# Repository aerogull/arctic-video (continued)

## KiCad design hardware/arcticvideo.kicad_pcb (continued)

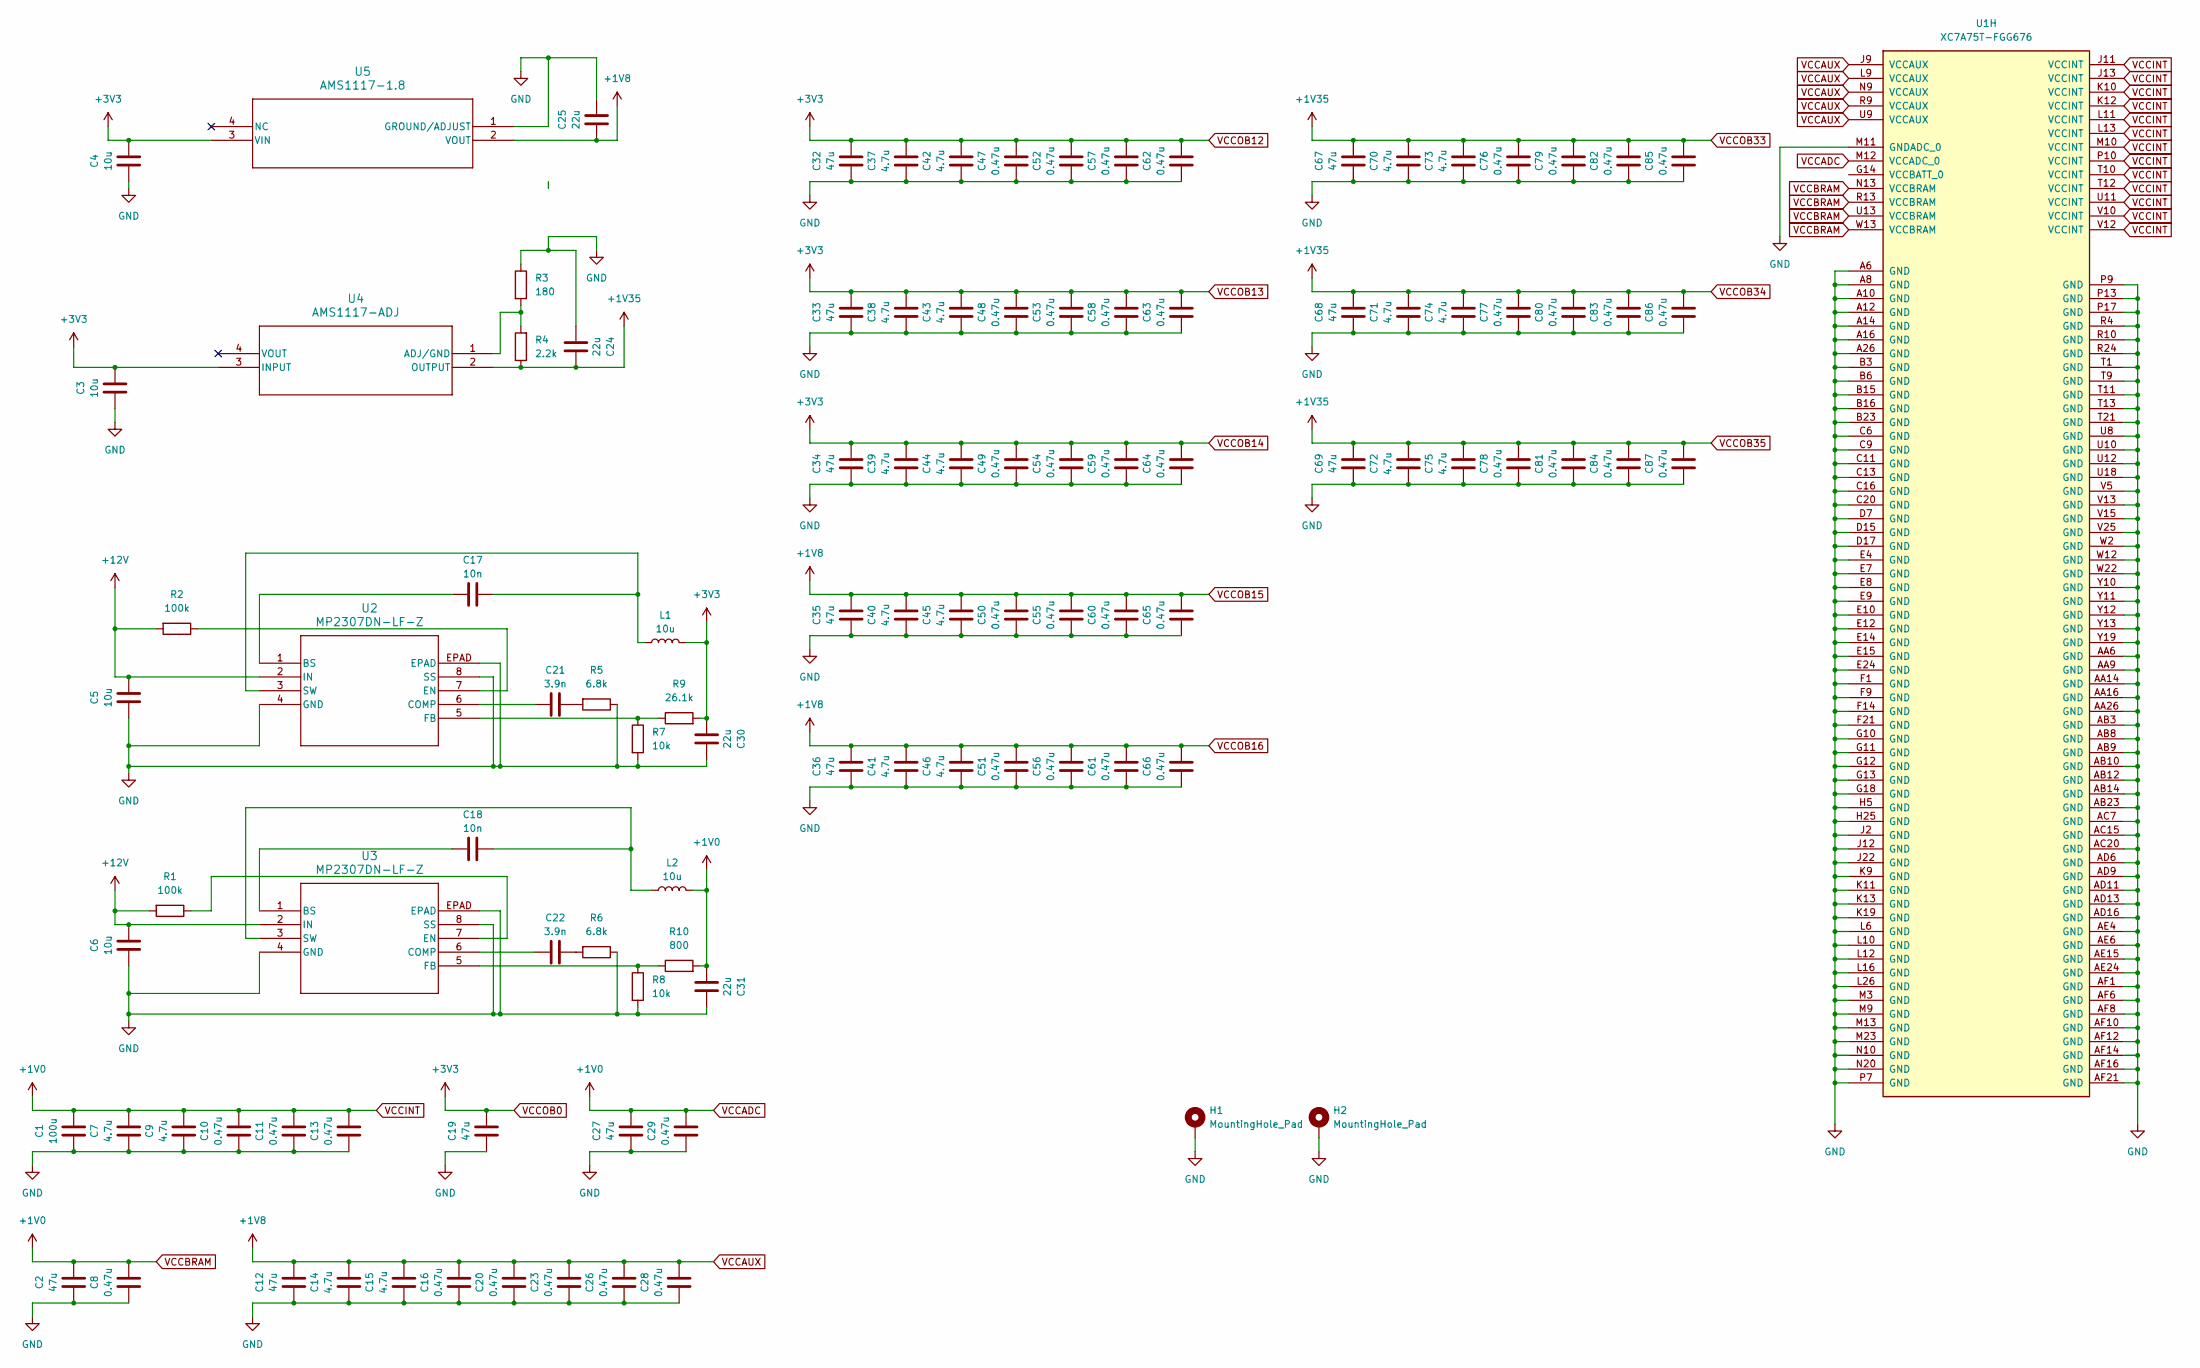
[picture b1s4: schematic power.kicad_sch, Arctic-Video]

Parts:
C1: 100u; C_0402_1005Metric
C2: 47u; C_0402_1005Metric
C3, C4, C5, C6: 10u; C_0402_1005Metric
C7, C9, C14, C15, C37, C38, C39, C40, C41, C42, C43, C44, C45, C46, C70, C71, C72, C73, C74, C75: 4.7u; C_0402_1005Metric
C8, C10, C11, C13, C16, C20, C23, C26, C28, C29, C47, C48, C49, C50, C51, C52, C53, C54, C55, C56, C57, C58, C59, C60, C61, C62, C63, C64, C65, C66, C76, C77, C78, C79, C80, C81, C82, C83, C84, C85, C86, C87: 0.47u; C_0402_1005Metric
C12, C19, C27, C32, C33, C34, C35, C36, C67, C68, C69: 47u; C_0603_1608Metric
C17, C18: 10n; C_0402_1005Metric
C21, C22: 3.9n; C_0402_1005Metric
C24, C25, C30, C31: 22u; C_0402_1005Metric
H1: MountingHole_Pad; MountingHole_2.7mm_Pad_Via
H2: MountingHole_Pad; MountingHole_3mm_Pad_Via
L1, L2: 10u; L_0402_1005Metric
R1, R2: 100k; R_0402_1005Metric
R3: 180; R_0402_1005Metric
R4: 2.2k; R_0402_1005Metric
R5, R6: 6.8k; R_0402_1005Metric
R7, R8: 10k; R_0402_1005Metric
R9: 26.1k; R_0402_1005Metric
R10: 800; R_0402_1005Metric
U1: XC7A75T-FGG676; Xilinx_FGG676
U2, U3: MP2307DN-LF-Z; IC8_MP2307_MNP
U4: AMS1117-ADJ; SOT_AMS1117-2.5_AMS
U5: AMS1117-1.8; SOT223_AMS1117-1.8_AMS

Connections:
+12V: C5.2, C6.2, R1.2, R2.2, U2.2 (IN), U3.2 (IN); also elsewhere on the board
GND: C1.1, C2.1, C3.1, C4.1, C5.1, C6.1, C7.1, C8.1, C9.1, C10.1, C11.1, C12.1, C13.1, C14.1, C15.1, C16.1, C19.1, C20.1, C23.1, C24.1, C25.2, C26.1, C27.1, C28.1, C29.1, C30.2, C31.2, C32.1, C33.1, C34.1, C35.1, C36.1, C37.1, C38.1, C39.1, C40.1, C41.1, C42.1, C43.1, C44.1, C45.1, C46.1, C47.1, C48.1, C49.1, C50.1, C51.1, C52.1, C53.1, C54.1, C55.1, C56.1, C57.1, C58.1, C59.1, C60.1, C61.1, C62.1, C63.1, C64.1, C65.1, C66.1, C67.1, C68.1, C69.1, C70.1, C71.1, C72.1, C73.1, C74.1, C75.1, C76.1, C77.1, C78.1, C79.1, C80.1, C81.1, C82.1, C83.1, C84.1, C85.1, C86.1, C87.1, H1.1 (1_1), H2.1 (1_1), R3.1, R5.1, R6.1, R7.2, R8.2, U1.A6 (GND), U1.A8 (GND), U1.A10 (GND), U1.A12 (GND), U1.A14 (GND), U1.A16 (GND), U1.A26 (GND), U1.AA6 (GND), U1.AA9 (GND), U1.AA14 (GND), U1.AA16 (GND), U1.AA26 (GND), U1.AB3 (GND), U1.AB8 (GND), U1.AB9 (GND), U1.AB10 (GND), U1.AB12 (GND), U1.AB14 (GND), U1.AB23 (GND), U1.AC7 (GND), U1.AC15 (GND), U1.AC20 (GND), U1.AD6 (GND), U1.AD9 (GND), U1.AD11 (GND), U1.AD13 (GND), U1.AD16 (GND), U1.AE4 (GND), U1.AE6 (GND), U1.AE15 (GND), U1.AE24 (GND), U1.AF1 (GND), U1.AF6 (GND), U1.AF8 (GND), U1.AF10 (GND), U1.AF12 (GND), U1.AF14 (GND), U1.AF16 (GND), U1.AF21 (GND), U1.B3 (GND), U1.B6 (GND), U1.B15 (GND), U1.B16 (GND), U1.B23 (GND), U1.C6 (GND), U1.C9 (GND), U1.C11 (GND), U1.C13 (GND), U1.C16 (GND), U1.C20 (GND), U1.D7 (GND), U1.D15 (GND), U1.D17 (GND), U1.E4 (GND), U1.E7 (GND), U1.E8 (GND), U1.E9 (GND), U1.E10 (GND), U1.E12 (GND), U1.E14 (GND), U1.E15 (GND), U1.E24 (GND), U1.F1 (GND), U1.F9 (GND), U1.F14 (GND), U1.F21 (GND), U1.G10 (GND), U1.G11 (GND), U1.G12 (GND), U1.G13 (GND), U1.G18 (GND), U1.H5 (GND), U1.H25 (GND), U1.J2 (GND), U1.J12 (GND), U1.J22 (GND), U1.K9 (GND), U1.K11 (GND), U1.K13 (GND), U1.K19 (GND), U1.L6 (GND), U1.L10 (GND), U1.L12 (GND), U1.L16 (GND), U1.L26 (GND), U1.M3 (GND), U1.M9 (GND), U1.M11 (GNDADC_0), U1.M13 (GND), U1.M23 (GND), U1.N10 (GND), U1.N20 (GND), U1.P7 (GND), U1.P9 (GND), U1.P13 (GND), U1.P17 (GND), U1.R4 (GND), U1.R10 (GND), U1.R24 (GND), U1.T1 (GND), U1.T9 (GND), U1.T11 (GND), U1.T13 (GND), U1.T21 (GND), U1.U8 (GND), U1.U10 (GND), U1.U12 (GND), U1.U18 (GND), U1.V5 (GND), U1.V13 (GND), U1.V15 (GND), U1.V25 (GND), U1.W2 (GND), U1.W12 (GND), U1.W22 (GND), U1.Y10 (GND), U1.Y11 (GND), U1.Y12 (GND), U1.Y13 (GND), U1.Y19 (GND), U2.4 (GND), U2.8 (SS), U2.EPAD, U3.4 (GND), U3.8 (SS), U3.EPAD, U5.1 (GROUND/ADJUST); also elsewhere on the board
unnamed: C21.2, R5.2
unnamed: C22.2, R6.2
unnamed: C17.1, U2.1 (BS)
unnamed: C21.1, U2.6 (COMP)
unnamed: R2.1, U2.7 (EN)
unnamed: R7.1, R9.1, U2.5 (FB)
unnamed: C17.2, L1.1, U2.3 (SW)
unnamed: C18.1, U3.1 (BS)
unnamed: C22.1, U3.6 (COMP)
unnamed: R1.1, U3.7 (EN)
unnamed: R8.1, R10.1, U3.5 (FB)
unnamed: C18.2, L2.1, U3.3 (SW)
unnamed: R3.2, R4.2, U4.1 (ADJ/GND)
VCCADC: C1.2, C2.2, C7.2, C8.2, C9.2, C10.2, C11.2, C13.2, C27.2, C29.2, C31.1, L2.2, R10.2, U1.J11 (VCCINT), U1.J13 (VCCINT), U1.K10 (VCCINT), U1.K12 (VCCINT), U1.L11 (VCCINT), U1.L13 (VCCINT), U1.M10 (VCCINT), U1.M12 (VCCADC_0), U1.N13 (VCCBRAM), U1.P10 (VCCINT), U1.R13 (VCCBRAM), U1.T10 (VCCINT), U1.T12 (VCCINT), U1.U11 (VCCINT), U1.U13 (VCCBRAM), U1.V10 (VCCINT), U1.V12 (VCCINT), U1.W13 (VCCBRAM)
VCCAUX: C12.2, C14.2, C15.2, C16.2, C20.2, C23.2, C25.1, C26.2, C28.2, C35.2, C36.2, C40.2, C41.2, C45.2, C46.2, C50.2, C51.2, C55.2, C56.2, C60.2, C61.2, C65.2, C66.2, U1.J9 (VCCAUX), U1.L9 (VCCAUX), U1.N9 (VCCAUX), U1.R9 (VCCAUX), U1.U9 (VCCAUX), U5.2 (VOUT); also elsewhere on the board
VCCOB0: C3.2, C4.2, C19.2, C30.1, C32.2, C33.2, C34.2, C37.2, C38.2, C39.2, C42.2, C43.2, C44.2, C47.2, C48.2, C49.2, C52.2, C53.2, C54.2, C57.2, C58.2, C59.2, C62.2, C63.2, C64.2, L1.2, R9.2, U4.3 (INPUT), U5.3 (VIN); also elsewhere on the board
VCCOB33: C24.2, C67.2, C68.2, C69.2, C70.2, C71.2, C72.2, C73.2, C74.2, C75.2, C76.2, C77.2, C78.2, C79.2, C80.2, C81.2, C82.2, C83.2, C84.2, C85.2, C86.2, C87.2, R4.1, U4.2 (OUTPUT); also elsewhere on the board

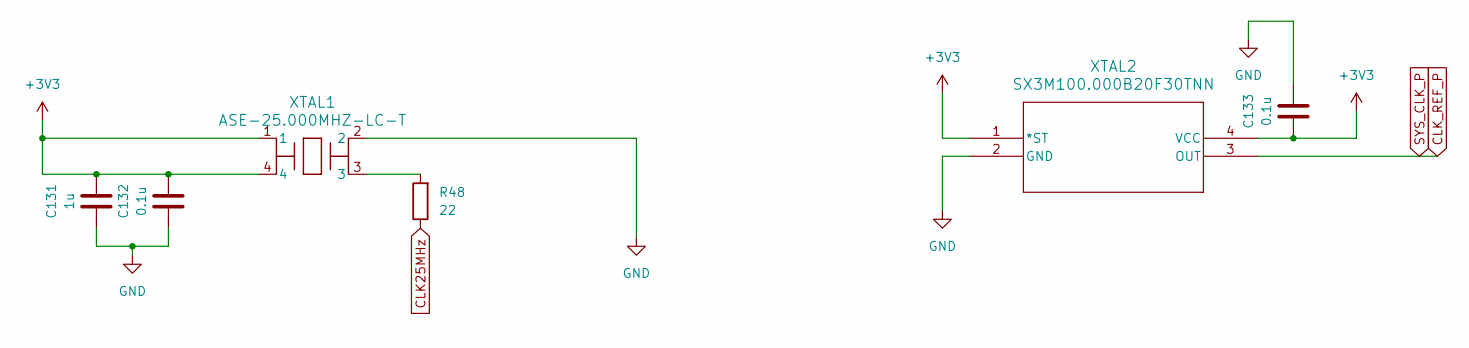
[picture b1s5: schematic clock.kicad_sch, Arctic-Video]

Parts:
C131: 1u; C_0402_1005Metric
C132, C133: 0.1u; C_0402_1005Metric
R48: 22; R_0402_1005Metric
XTAL1: ASE-25.000MHZ-LC-T; CHIP_ASE-24_ABR
XTAL2: SX3M100.000B20F30TNN; SG-210STF_EPS

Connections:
CLK25MHz: R48.1; also elsewhere on the board
CLK_REF_P: XTAL2.3 (OUT); also elsewhere on the board
GND: C131.1, C132.1, C133.2, XTAL1.2, XTAL2.2 (GND); also elsewhere on the board
unnamed: R48.2, XTAL1.3
VCCOB0: C131.2, C132.2, C133.1, XTAL1.1, XTAL1.4, XTAL2.1 (*ST), XTAL2.4 (VCC); also elsewhere on the board

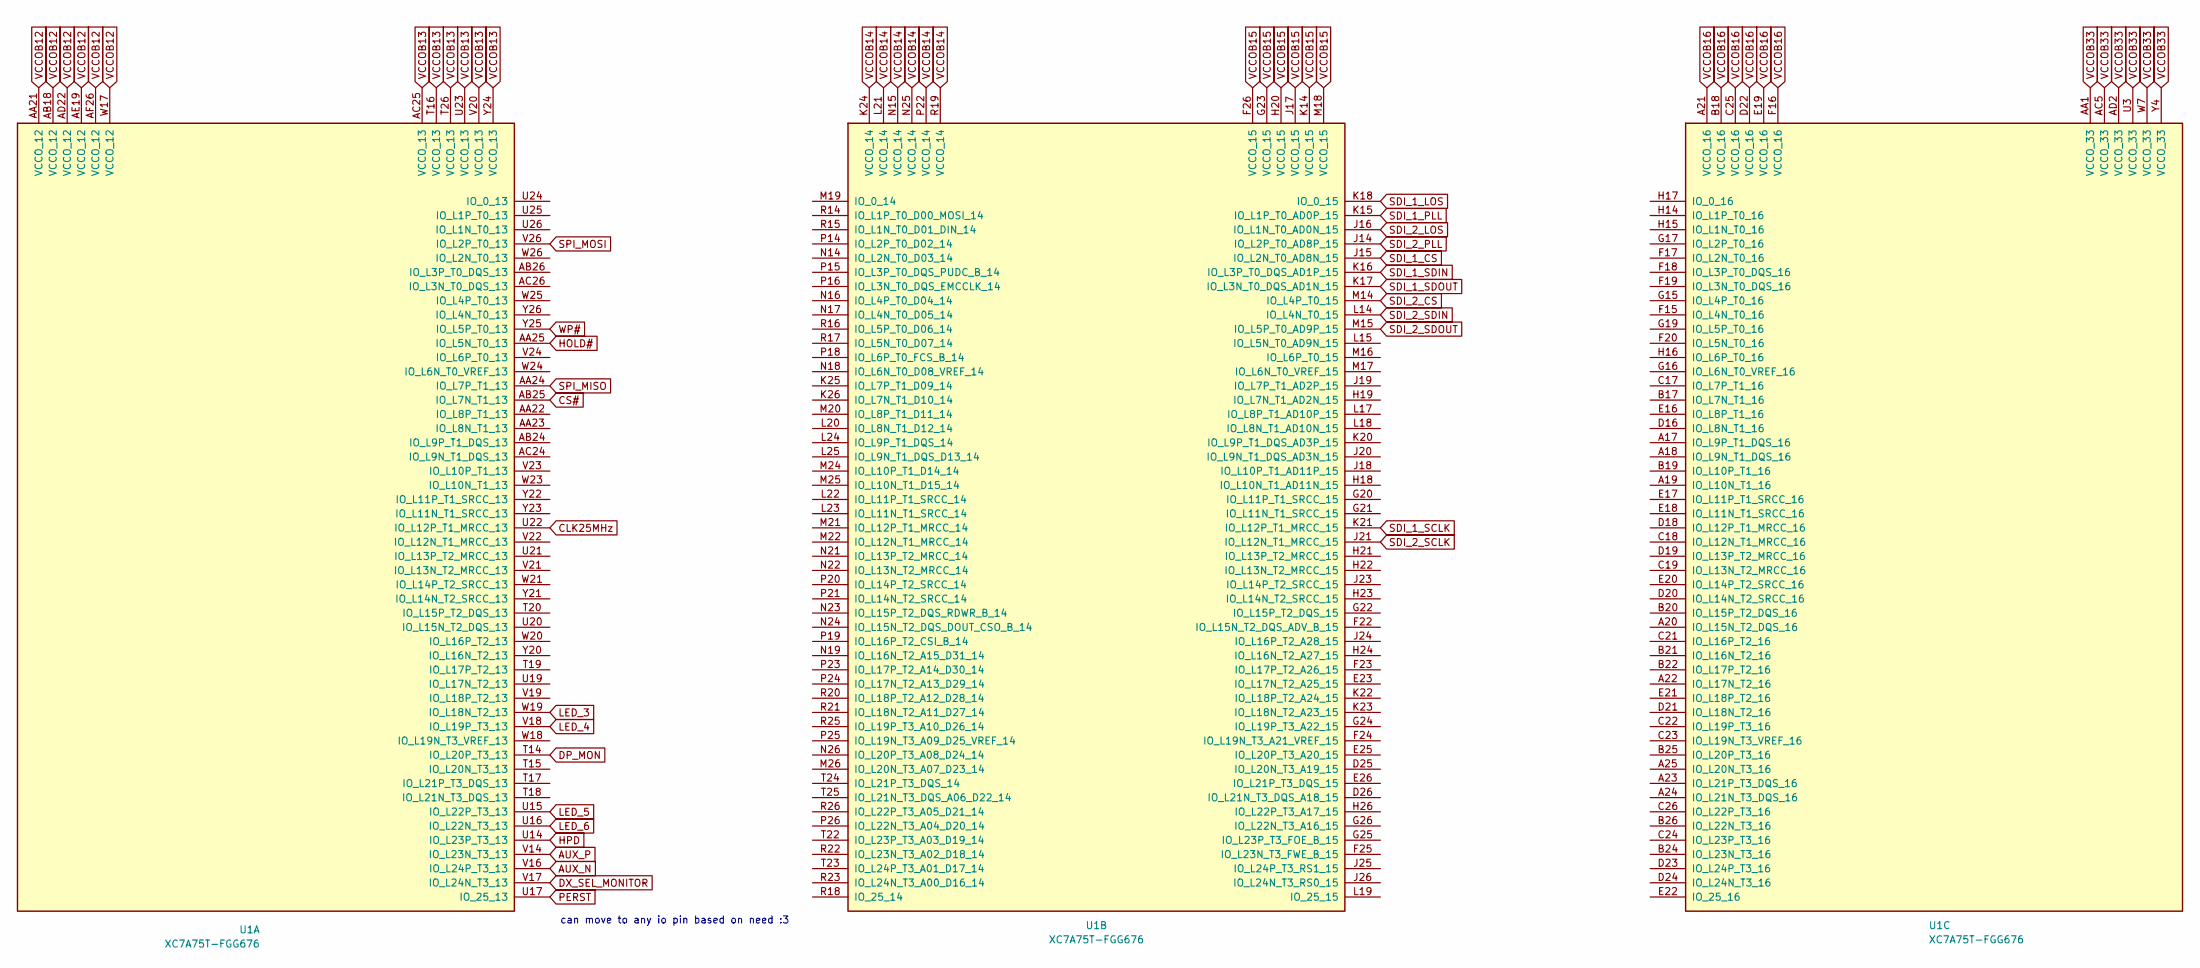
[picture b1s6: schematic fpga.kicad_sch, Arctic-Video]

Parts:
U1: XC7A75T-FGG676; Xilinx_FGG676

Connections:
AUX_N: U1.V16 (IO_L24P_T3_13); also elsewhere on the board
AUX_P: U1.V14 (IO_L23N_T3_13); also elsewhere on the board
CLK25MHz: U1.U22 (IO_L12P_T1_MRCC_13); also elsewhere on the board
CS#: U1.AB25 (IO_L7N_T1_13); also elsewhere on the board
DP_MON: U1.T14 (IO_L20P_T3_13); also elsewhere on the board
DX_SEL_MONITOR: U1.V17 (IO_L24N_T3_13); also elsewhere on the board
HOLD#: U1.AA25 (IO_L5N_T0_13); also elsewhere on the board
HPD: U1.U14 (IO_L23P_T3_13); also elsewhere on the board
LED_3: U1.W19 (IO_L18N_T2_13); also elsewhere on the board
LED_4: U1.V18 (IO_L19P_T3_13); also elsewhere on the board
LED_5: U1.U15 (IO_L22P_T3_13); also elsewhere on the board
LED_6: U1.U16 (IO_L22N_T3_13); also elsewhere on the board
PERST: U1.U17 (IO_25_13); also elsewhere on the board
SDI_1_CS: U1.J15 (IO_L2N_T0_AD8N_15); also elsewhere on the board
SDI_1_LOS: U1.K18 (IO_0_15); also elsewhere on the board
SDI_1_PLL: U1.K15 (IO_L1P_T0_AD0P_15); also elsewhere on the board
SDI_1_SCLK: U1.K21 (IO_L12P_T1_MRCC_15); also elsewhere on the board
SDI_1_SDIN: U1.K16 (IO_L3P_T0_DQS_AD1P_15); also elsewhere on the board
SDI_1_SDOUT: U1.K17 (IO_L3N_T0_DQS_AD1N_15); also elsewhere on the board
SDI_2_CS: U1.M14 (IO_L4P_T0_15); also elsewhere on the board
SDI_2_LOS: U1.J16 (IO_L1N_T0_AD0N_15); also elsewhere on the board
SDI_2_PLL: U1.J14 (IO_L2P_T0_AD8P_15); also elsewhere on the board
SDI_2_SCLK: U1.J21 (IO_L12N_T1_MRCC_15); also elsewhere on the board
SDI_2_SDIN: U1.L14 (IO_L4N_T0_15); also elsewhere on the board
SDI_2_SDOUT: U1.M15 (IO_L5P_T0_AD9P_15); also elsewhere on the board
SPI_MISO: U1.AA24 (IO_L7P_T1_13); also elsewhere on the board
SPI_MOSI: U1.V26 (IO_L2P_T0_13); also elsewhere on the board
VCCAUX: U1.A21 (VCCO_16), U1.B18 (VCCO_16), U1.C25 (VCCO_16), U1.D22 (VCCO_16), U1.E19 (VCCO_16), U1.F16 (VCCO_16), U1.F26 (VCCO_15), U1.G23 (VCCO_15), U1.H20 (VCCO_15), U1.J17 (VCCO_15), U1.K14 (VCCO_15), U1.M18 (VCCO_15); also elsewhere on the board
VCCOB0: U1.AA21 (VCCO_12), U1.AB18 (VCCO_12), U1.AC25 (VCCO_13), U1.AD22 (VCCO_12), U1.AE19 (VCCO_12), U1.AF26 (VCCO_12), U1.K24 (VCCO_14), U1.L21 (VCCO_14), U1.N15 (VCCO_14), U1.N25 (VCCO_14), U1.P22 (VCCO_14), U1.R19 (VCCO_14), U1.T16 (VCCO_13), U1.T26 (VCCO_13), U1.U23 (VCCO_13), U1.V20 (VCCO_13), U1.W17 (VCCO_12), U1.Y24 (VCCO_13); also elsewhere on the board
VCCOB33: U1.AA1 (VCCO_33), U1.AC5 (VCCO_33), U1.AD2 (VCCO_33), U1.U3 (VCCO_33), U1.W7 (VCCO_33), U1.Y4 (VCCO_33); also elsewhere on the board
WP#: U1.Y25 (IO_L5P_T0_13); also elsewhere on the board

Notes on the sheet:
can move to any io pin based on need :3

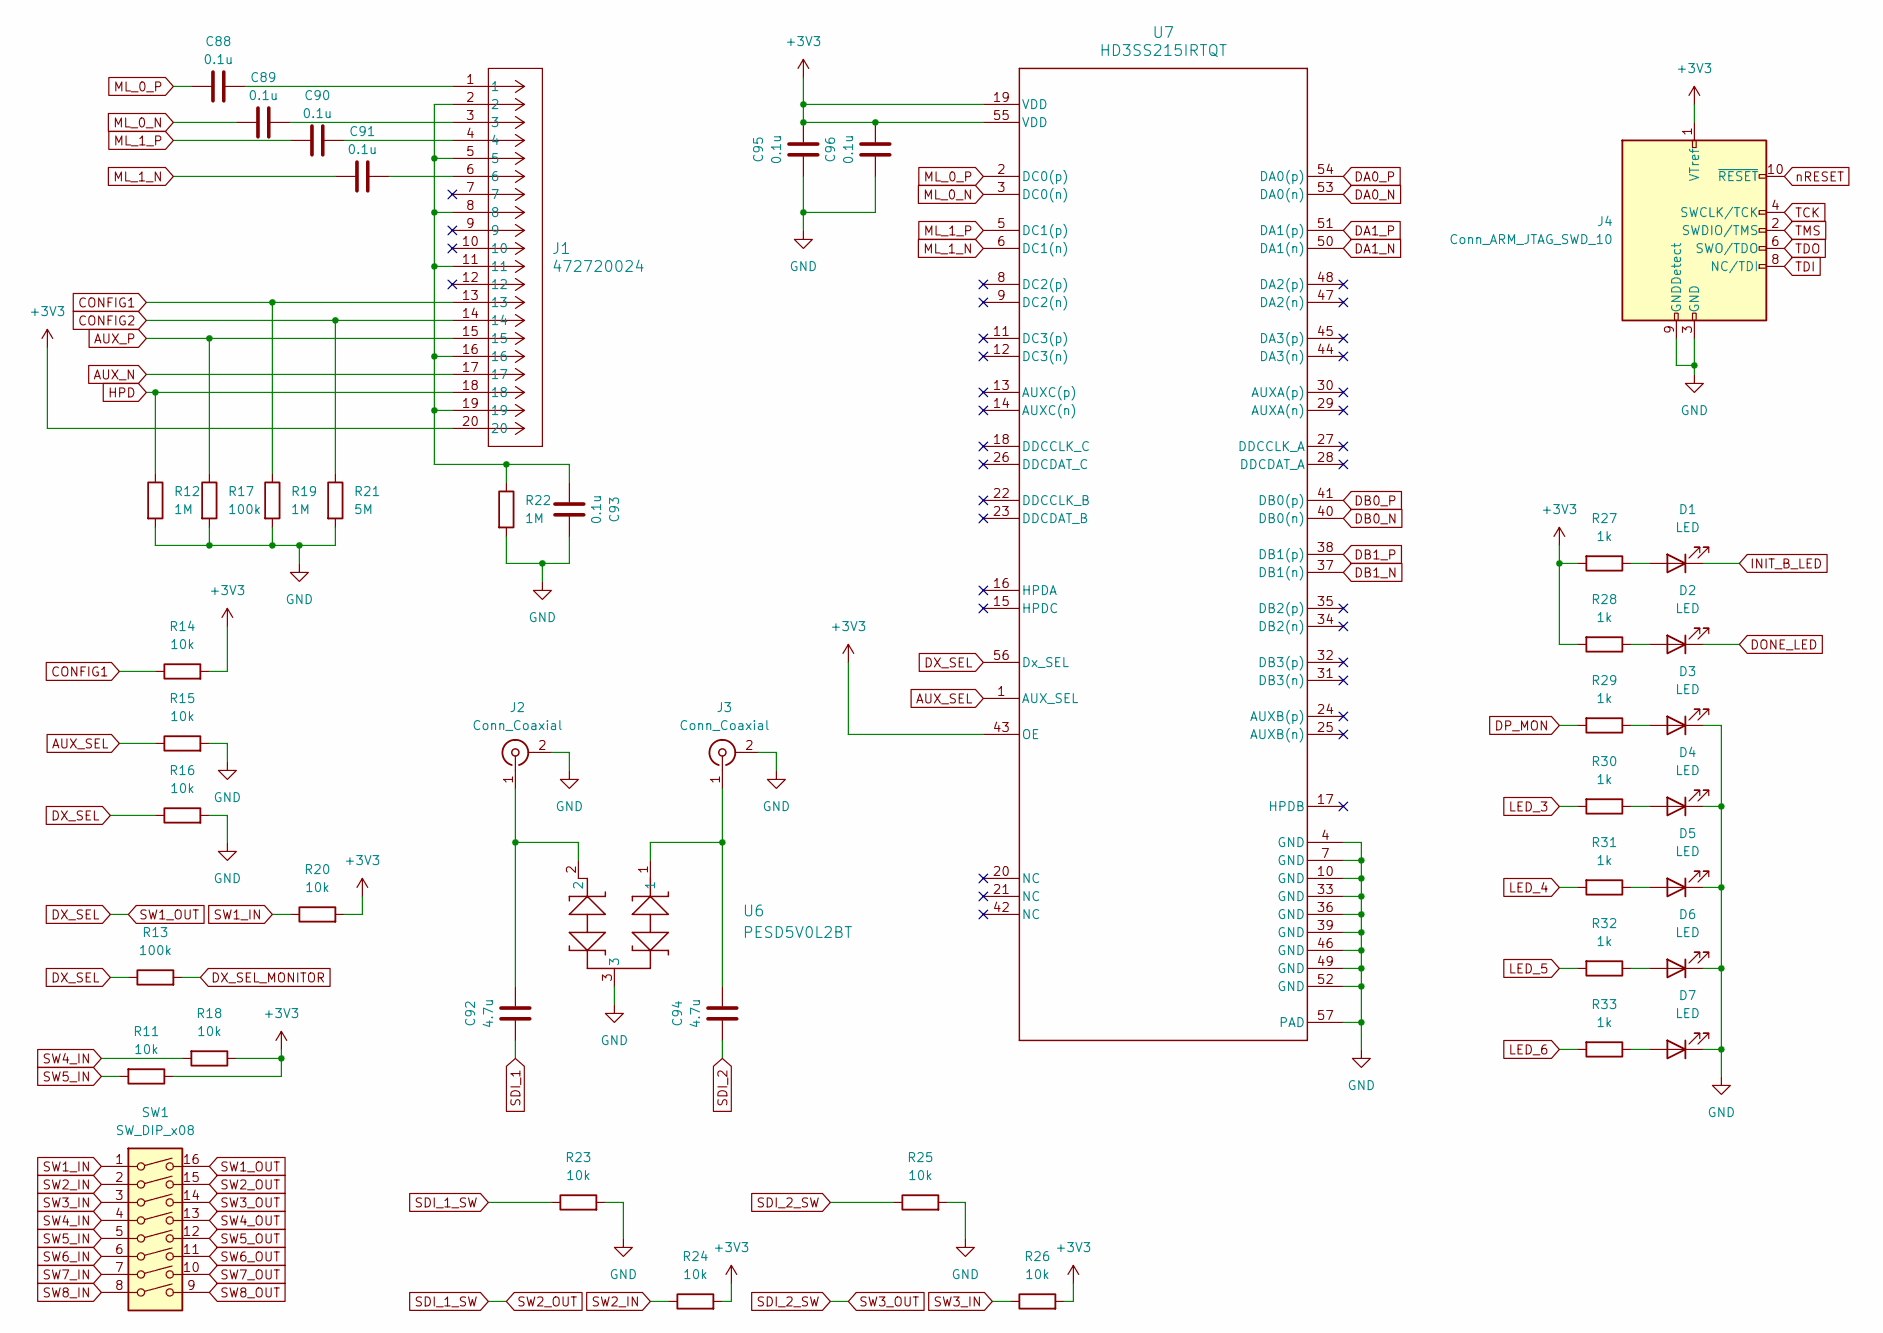
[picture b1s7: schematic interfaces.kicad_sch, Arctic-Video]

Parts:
C88, C89, C90, C91, C93, C95, C96: 0.1u; C_0402_1005Metric
C92, C94: 4.7u; C_0402_1005Metric
D1, D2, D3, D4, D5, D6, D7: LED; LED_0402_1005Metric
J1: 472720024; CONN_47272-0024_MOL
J2, J3: Conn_Coaxial; SAMTEC_BNC7T-J-P-XX-ST-EM1D
J4: Conn_ARM_JTAG_SWD_10; PinSocket_2x05_P2.54mm_Vertical
R11, R14, R15, R16, R18, R20, R23, R24, R25, R26: 10k; R_0402_1005Metric
R12, R19, R22: 1M; R_0402_1005Metric
R13, R17: 100k; R_0402_1005Metric
R21: 5M; R_0402_1005Metric
R27, R28, R29, R30, R31, R32, R33: 1k; R_0402_1005Metric
SW1: SW_DIP_x08; SW_DIP_SPSTx08_Slide_9.78x22.5mm_W7.62mm_P2.54mm
U6: PESD5V0L2BT; SOT23_NEX
U7: HD3SS215IRTQT; RTQ0056B

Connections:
AUX_N: J1.17; also elsewhere on the board
AUX_P: J1.15, R17.1; also elsewhere on the board
AUX_SEL: R15.1, U7.1 (AUX_SEL)
CONFIG1: J1.13, R14.1, R19.1
CONFIG2: J1.14, R21.1
DA0_N: U7.53 (DA0(n)); also elsewhere on the board
DA0_P: U7.54 (DA0(p)); also elsewhere on the board
DA1_N: U7.50 (DA1(n)); also elsewhere on the board
DA1_P: U7.51 (DA1(p)); also elsewhere on the board
DB0_N: U7.40 (DB0(n)); also elsewhere on the board
DB0_P: U7.41 (DB0(p)); also elsewhere on the board
DB1_N: U7.37 (DB1(n)); also elsewhere on the board
DB1_P: U7.38 (DB1(p)); also elsewhere on the board
DONE_LED: D2.1 (K); also elsewhere on the board
DP_MON: R29.2; also elsewhere on the board
DX_SEL: R13.1, R16.1, SW1.16, U7.56 (Dx_SEL)
DX_SEL_MONITOR: R13.2; also elsewhere on the board
GND: C93.2, C95.1, C96.1, D3.1 (K), D4.1 (K), D5.1 (K), D6.1 (K), D7.1 (K), J2.2 (Ext), J3.2 (Ext), J4.3 (GND), J4.5 (GND), J4.9 (GNDDetect), R12.2, R15.2, R16.2, R17.2, R19.2, R21.2, R22.2, R23.2, R25.2, U6.3, U7.4 (GND), U7.7 (GND), U7.10 (GND), U7.33 (GND), U7.36 (GND), U7.39 (GND), U7.46 (GND), U7.49 (GND), U7.52 (GND), U7.57 (PAD); also elsewhere on the board
HPD: J1.18, R12.1; also elsewhere on the board
INIT_B_LED: D1.1 (K); also elsewhere on the board
LED_3: R30.2; also elsewhere on the board
LED_4: R31.2; also elsewhere on the board
LED_5: R32.2; also elsewhere on the board
LED_6: R33.2; also elsewhere on the board
ML_0_N: C89.1, U7.3 (DC0(n))
ML_0_P: C88.1, U7.2 (DC0(p))
ML_1_N: C91.1, U7.6 (DC1(n))
ML_1_P: C90.1, U7.5 (DC1(p))
unnamed: C88.2, J1.1
unnamed: C89.2, J1.3
unnamed: C90.2, J1.4
unnamed: C91.2, J1.6
unnamed: C93.1, J1.2, J1.5, J1.8, J1.11, J1.16, J1.19, R22.1
unnamed: D1.2 (A), R27.1
unnamed: D2.2 (A), R28.1
unnamed: D3.2 (A), R29.1
unnamed: D4.2 (A), R30.1
unnamed: D5.2 (A), R31.1
unnamed: D6.2 (A), R32.1
unnamed: D7.2 (A), R33.1
unnamed: C92.2, J2.1 (In_1), U6.2
unnamed: C94.2, J3.1 (In_1), U6.1
SDI_1: C92.1; also elsewhere on the board
SDI_1_SW: R23.1, SW1.15
SDI_2: C94.1; also elsewhere on the board
SDI_2_SW: R25.1, SW1.14
SW1_IN: R20.1, SW1.1
SW2_IN: R24.1, SW1.2
SW3_IN: R26.1, SW1.3
SW4_IN: R18.2, SW1.4
SW4_OUT: SW1.13; also elsewhere on the board
SW5_IN: R11.2, SW1.5
SW5_OUT: SW1.12; also elsewhere on the board
SW6_IN: SW1.6
SW6_OUT: SW1.11
SW7_IN: SW1.7
SW7_OUT: SW1.10
SW8_IN: SW1.8
SW8_OUT: SW1.9
TCK: J4.4 (SWCLK/TCK); also elsewhere on the board
TDI: J4.8 (NC/TDI); also elsewhere on the board
TDO: J4.6 (SWO/TDO); also elsewhere on the board
TMS: J4.2 (SWDIO/TMS); also elsewhere on the board
VCCOB0: C95.2, C96.2, J1.20, J4.1 (VTref), R11.1, R14.2, R18.1, R20.2, R24.2, R26.2, R27.2, R28.2, U7.19 (VDD), U7.43 (OE), U7.55 (VDD); also elsewhere on the board
nRESET: J4.10 (~RESET); also elsewhere on the board

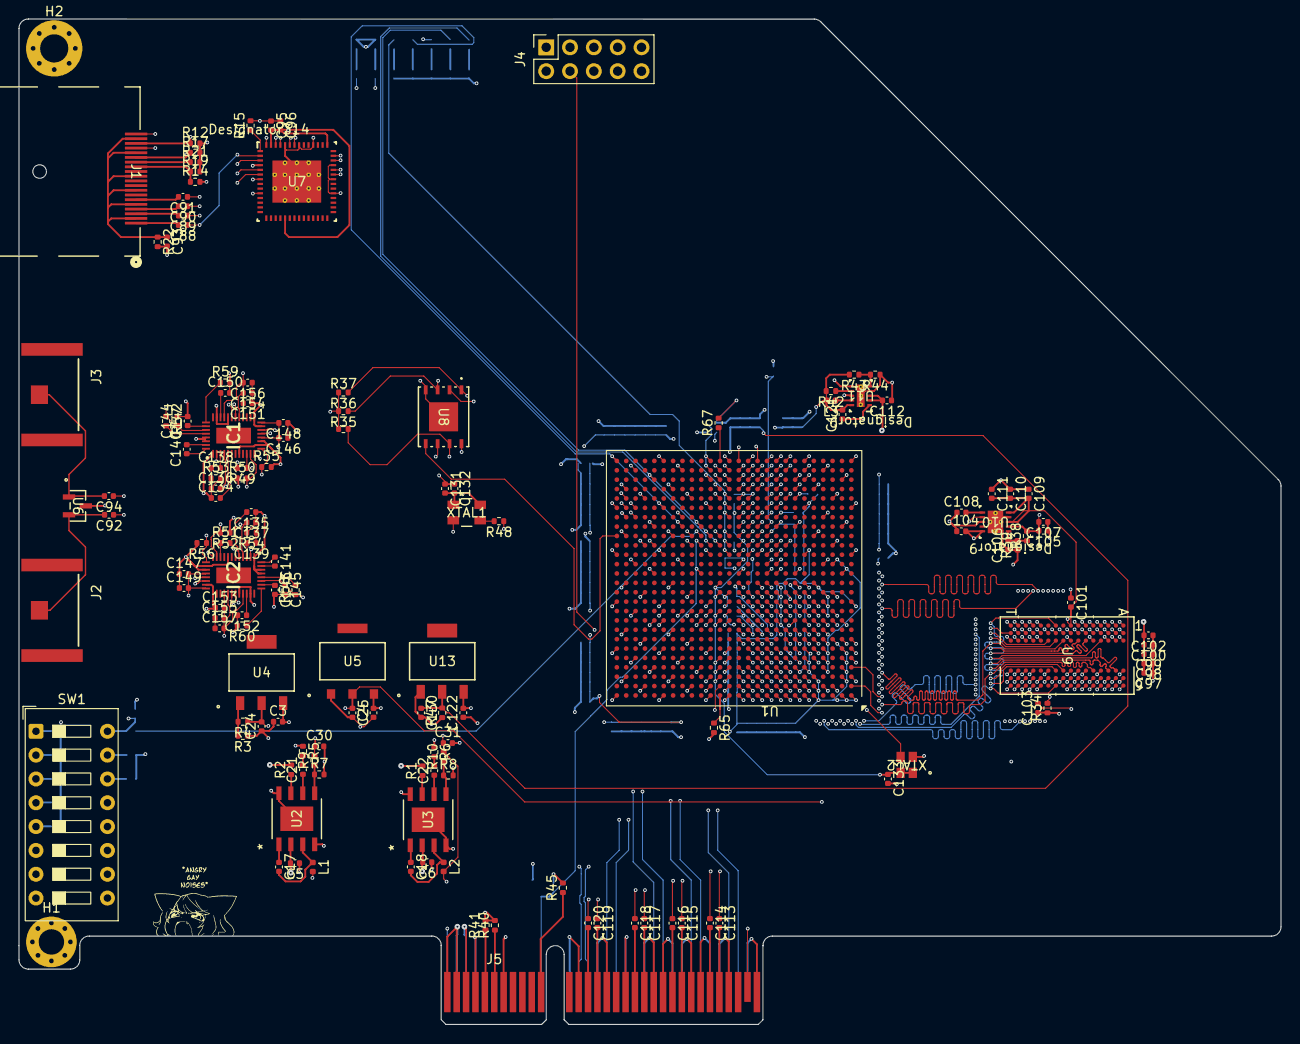
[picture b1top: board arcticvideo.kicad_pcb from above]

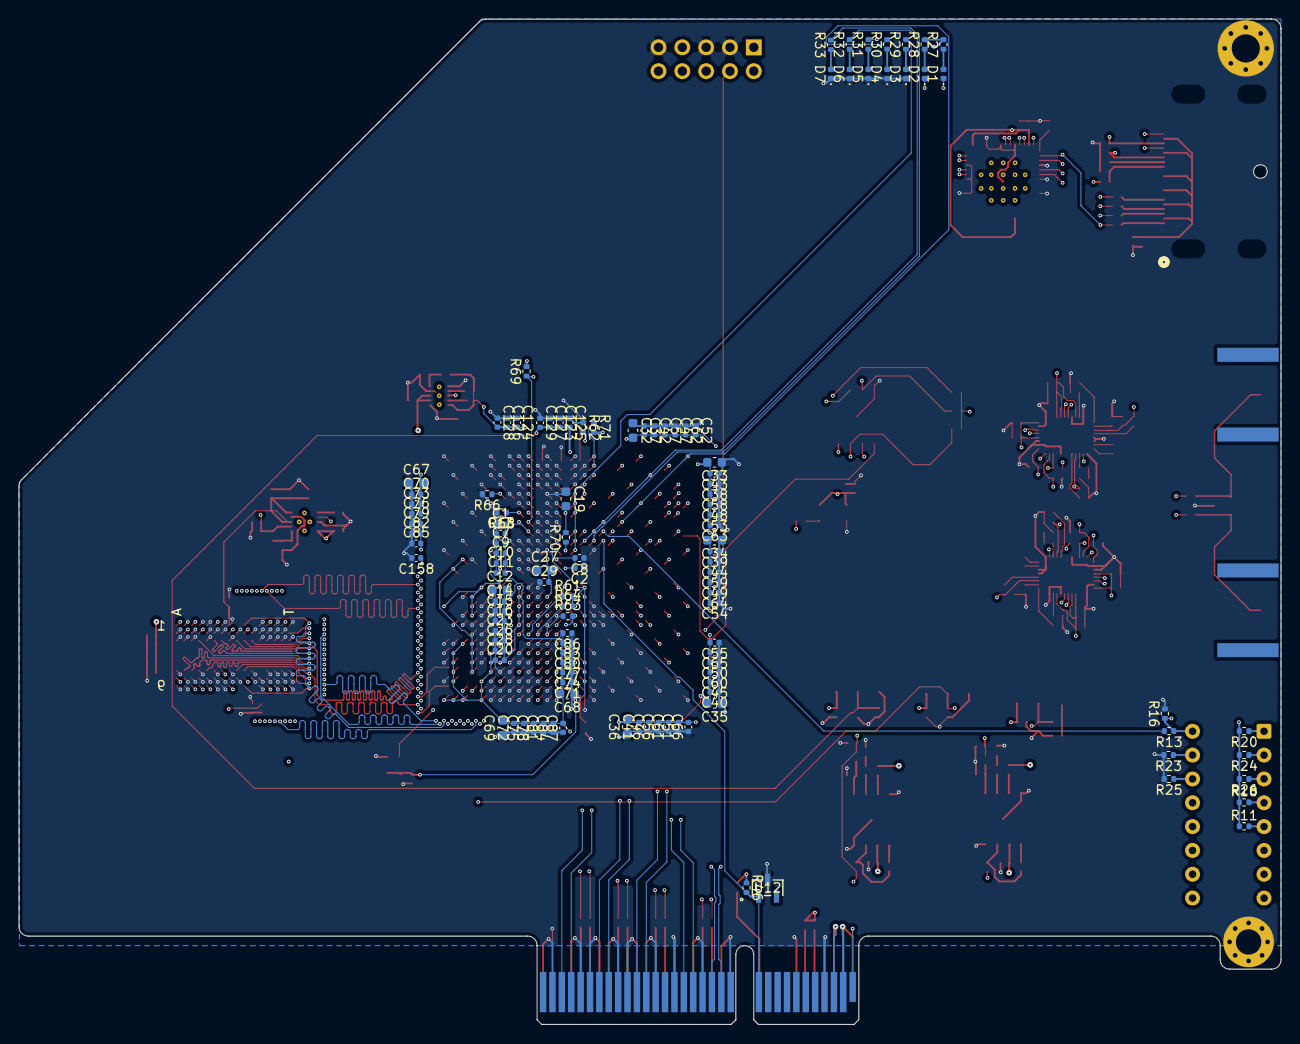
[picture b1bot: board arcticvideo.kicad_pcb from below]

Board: 8 copper layers, 134.5 x 107.2 mm, 264 parts (117 on the bottom side), 213 nets.

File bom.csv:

Designator,Footprint,Quantity,Value,LCSC Part #
C1,0402,1,100u,
"C10, C11, C13, C16, C20, C23, C26, C28, C29, C47, C48, C49, C50, C51, C52, C53, C54, C55, C56, C57, C58, C59, C60, C61, C62, C63, C64, C65, C66, C76, C77, C78, C79, C8, C80, C81, C82, C83, C84, C85, C86, C87",0402,42,0.47u,
"C100, C101, C102, C103, C108, C126, C127, C128, C129, C132, C133, C158, C88, C89, C90, C91, C93, C95, C96, C98, C99",0402,21,0.1u,
"C104, C123, C124, C125, C138, C139, C14, C15, C37, C38, C39, C40, C41, C42, C43, C44, C45, C46, C7, C70, C71, C72, C73, C74, C75, C9, C92, C94, C97",0402,29,4.7u,
"C105, C107, C109, C110, C111, C122, C142, C143, C144, C145, C150, C152, C3, C4, C5, C6, L1, L2, L3",0402,19,10u,
C106,0402,1,1000p,
C112,0402,1,2.2u,
"C113, C114, C115, C116, C117, C118, C119, C120, C134, C135, C146, C147, C148, C149, C151, C153, C154, C155, C156, C157",0402,20,100n,
"C12, C19, C27, C32, C33, C34, C35, C36, C67, C68, C69",0603,11,47u,
"C121, C130, C24, C25, C30, C31",0402,6,22u,
"C131, C136, C137",0402,3,1u,
"C140, C141",0402,2,470n,
"C17, C18",0402,2,10n,
C2,0402,1,47u,
"C21, C22",0402,2,3.9n,
"D1, D2, D3, D4, D5, D6, D7",0402,7,LED,
"IC1, IC2",QFN40P400X600X100-41N-D,2,GS12142,
J1,CONN_47272-0024_MOL,1,472720024,
"J2, J3",SAMTEC_BNC7T-J-P-XX-ST-EM1D,2,Conn_Coaxial,
J4,PinSocket_2x05_P2.54mm_Vertical,1,Conn_ARM_JTAG_SWD_10,
J5,BUS_PCIexpress_x4,1,Bus_PCI_Express_x4,
"R1, R13, R17, R2, R42, R44, R49, R50, R51, R52, R55, R56, R57, R58, R59, R60",0402,16,100k,
R10,0402,1,800,
"R11, R14, R15, R16, R18, R20, R23, R24, R25, R26, R35, R36, R37, R38, R39, R40, R41, R45, R46, R61, R62, R64, R66, R68, R69, R7, R70, R71, R8",0402,29,10k,
"R12, R19, R22",0402,3,1M,
R21,0402,1,5M,
"R27, R28, R29, R30, R31, R32, R33, R47",0402,8,1k,
R3,0402,1,180,
R34,0402,1,240,
R4,0402,1,2.2k,
R43,0402,1,24.9k,
R48,0402,1,22,
"R5, R6",0402,2,6.8k,
"R53, R54",0402,2,2,
R63,0402,1,100,
"R65, R67",0402,2,12.1k,
R9,0402,1,26.1k,
SW1,SW_DIP_SPSTx08_Slide_9.78x22.5mm_W7.62mm_P2.54mm,1,SW_DIP_x08,
U1,Xilinx_FGG676,1,XC7A75T-FGG676,
U10,DRC0010J,1,TPS51200DRCR,
U11,DQC0010A,1,TPS62175DQCR,
"U12, U6",SOT23_NEX,2,PESD5V0L2BT,
"U13, U4",SOT_AMS1117-2.5_AMS,2,AMS1117-ADJ,
"U2, U3",IC8_MP2307_MNP,2,MP2307DN-LF-Z,
U5,SOT223_AMS1117-1.8_AMS,1,AMS1117-1.8,
U7,RTQ0056B,1,HD3SS215IRTQT,
U8,SON_EW7-0SIT_MRN,1,MT25QL256ABA1EW7-0SIT,
U9,FBGA96_8X14_MRN,1,MT41K256M16TW-107:P,
XTAL1,CHIP_ASE-24_ABR,1,ASE-25.000MHZ-LC-T,
XTAL2,SG-210STF_EPS,1,SX3M100.000B20F30TNN,

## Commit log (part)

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2026-06-18 init
2026-06-19 finished pcie interface
2026-06-21 last commit for a while, i have to change the fpga and i dont have the time, money, or motivation to do that
2026-06-23 finished schematic!!! :D (before peer review)
2026-06-24 small changes
2026-06-24 readable changes
2026-06-26 pcb routing
2026-06-26 pcb changes v2
